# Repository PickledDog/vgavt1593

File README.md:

# vgavt1593
 Marco Maccaferri's Propeller VT100 Terminal, in a box

## Overview
This is a remix of Marco Maccaferri's [VGA Serial Terminal](https://github.com/maccasoft/propeller-vt100-terminal) for RC2014. It is specifically adapted to be used with Stephen C Cousins' [SC131](https://smallcomputercentral.wordpress.com/sc131-z180-pocket-computer/) Z180 pocket computer. It fits into the same Hammond 1593N enclosure, making for a neat and tidy setup when combined with an SC131. Of course, it can also be used with any other retrocomputer or device that expects a VT100-like terminal, connected over "TTL-Serial" raw RS232.

VGA terminal stacked with SC131 computer

## Terminal description
Details about the terminal itself are covered by Marco's project (this remix largely just changes the form factor). For detailed information, see his [project page](https://github.com/maccasoft/propeller-vt100-terminal).

## Serial interfaces
Connection to a computer is provided through an FTDI-style pin header, wired to the same pinout. Specifically, it is wired as a DTE (just like an FTDI dongle), so it can be wired directly to a DCE (like an SC131). A second *passthrough* port is provided to permit a PC connection to the same computer. This passthrough port is wired as a DCE, so FTDI cables can be connected directly. An AND gate mixes the terminal and passthrough connections together, so both can be used simultaneously. Transmitting from both at the same time will send gibberish; in testing this is relatively rare, and XMODEM at least will retransmit if this happens.

## Usage
This terminal lets you use your SC131 (or other retrocomputer) standalone, without dependency on another computer. In addition, a modern computer can be connected to the passthrough port as needed. This is useful for sending files over XMODEM, for example.

### Power
5V power is received through a standard 5.5/2.1mm barrel jack connection, center positive. The device optionally sends power to the connected computer (selectable by a jumper on JP1 - this is expected by SC131). In most cases, JP1 should be left installed. Wall adapters in this voltage and configuration are common, or a USB to 5.5mm cable can be used (examples [here](https://www.ebay.com/sch/i.html?_nkw=usb+to+5.5mm)).

### Why are the plugs on the front?
Because I ran out of room on the enclosure's panels. Between two FTDI headers, 5V in, reset, power switch, VGA, and USB, there wasn't even room left for a power LED. The serial ports are on the same side as the SC131 ones at least, so those can be connected together cleanly with a [6-pin Dupont cable](https://www.ebay.com/sch/i.html?_nkw=6+pin+dupont+cable).

### Initial setup
The parts specified are not pre-programmed; they will need to be programmed before use. Either a [Prop-Plug](https://www.mouser.com/ProductDetail/32201) can be used on the assembled board, or a [TL866](https://www.ebay.com/sch/i.html?_nkw=tl866ii+plus) or [CH341](https://www.ebay.com/sch/i.html?_nkw=ch341a+programmer) can be used on the bare EEPROM. Instructions (and firmware) for programming can be found at the same [link](https://github.com/maccasoft/propeller-vt100-terminal) as above.

## Part selection
Bill Of Materials and part references are below. Note that the right-angle headers have to be a specific type to align with the panel PCBs - they need to have the plastic "end stopper" on the "business" side of the angle, *not* the side you solder to the PCB. Headers from [Pololu](https://www.pololu.com/product/967), [Sparkfun](https://www.sparkfun.com/products/553), and [Adafruit](https://www.adafruit.com/product/1540) are like this, as is the Mouser listing below. Most eBay etc listings are ***not*** like this, and will not align correctly. If the appropriate headers cannot be sourced, double-row right-angle headers can be used, with the top row of pins removed.

The other headers can be snapped from regular breakaway header, for which eBay is substantially cheaper; the Mouser listings are provided for convenience. The specified parts are just the ones I used, and can be substituted as needed - Mouser links provided for convenience and reference. The case is available in other colours!

| Reference | Value | Qty | Mouser link |
| --------- | ----- | --- | ----------- |
| BZ1 | Piezo buzzer | 1 | [TDK PS1240P02BT](https://www.mouser.com/ProductDetail/810-PS1240P02BT) |
| C1, C2 | 1μF ceramic | 2 | [TDK FG18X5R1H105KRT06](https://www.mouser.com/ProductDetail/FG18X5R1H105KRT06) |
| C3-C7 | 100nF ceramic | 5 | [KEMET C315C104M5U5TA](https://www.mouser.com/ProductDetail/C315C104M5U5TA7303) |
| C8 | 10μF electrolytic | 1 | [Nichicon UMA1E100MDD](https://www.mouser.com/ProductDetail/UMA1E100MDD) |
| J1 | 5.5/2.1mm barrel socket | 1 | [CUI PJ-002A](https://www.mouser.com/ProductDetail/490-PJ-002A) |
| J2 | 1x4 header | 1 | [Amphenol 10129378-904002BLF](https://www.mouser.com/ProductDetail/10129378-904002BLF) |
| J3, J4 | 1x6 right-angle header | 2 | [Amphenol 10129379-906003BLF](https://www.mouser.com/ProductDetail/10129379-906003BLF) |
| J5 | USB A socket | 1 | [Amphenol FCI 87520-1110BLF](https://www.mouser.com/ProductDetail/649-87520-1110BLF) |
| J6 | D-Sub HD-15 Female | 1 | [TE 2311763-1](https://www.mouser.com/ProductDetail/571-2311763-1) |
| JP1 | 1x2 header | 1 | [Amphenol 10129378-902002BLF](https://www.mouser.com/ProductDetail/10129378-902002BLF) |
| | jumper | 1 | [Harwin M7583-46](https://www.mouser.com/ProductDetail/M7583-46)
| R1, R4 | 10kΩ resistor | 2 | [Yageo CFR-25JT-52-10K](https://www.mouser.com/ProductDetail/CFR-25JT-52-10K) |
| R2, R3 | 4k7Ω resistor | 2 | [Yageo CFR-25JT-52-4K7](https://www.mouser.com/ProductDetail/CFR-25JT-52-4K7) |
| R5, R8 | 47kΩ resistor | 2 | [Yageo CFR-25JT-52-47K](https://www.mouser.com/ProductDetail/CFR-25JT-52-47K) |
| R6, R7 | 47Ω resistor | 2 | [Yageo CFR-25JT-52-47R](https://www.mouser.com/ProductDetail/CFR-25JT-52-47R) |
| R9, R12, R15 | 261Ω resistor | 3 | [Yageo MFR-25FRF52-261R](https://www.mouser.com/ProductDetail/603-MFR-25FRF52-261R) |
| R10, R13, R16 | 510Ω resistor | 3 | [Yageo MFR-25FTE52-510R](https://www.mouser.com/ProductDetail/603-MFR-25FTE52-510R) |
| R11, R14, R17-R19 | 120Ω resistor | 5 | [Yageo MFR-25FTF52-120R](https://www.mouser.com/ProductDetail/603-MFR-25FTF52-120R) |
| SW1 | SPDT toggle sw, right-angle | 1 | [Grayhill 34CMSP12B2M7QT](https://www.mouser.com/ProductDetail/706-34CMSP12B2M7QT) |
| SW2 | Right-angle tact sw 8.3mm | 1 | [C&K PTS645VL832LFS](https://www.mouser.com/ProductDetail/611-PTS645VL832) |
| U1 | Parallax Propeller | 1 | [Parallax Propeller P8X32A-D40](https://www.mouser.com/ProductDetail/619-P8X32A-D40) |
| | socket | 1 | [Amphenol DILB40P-223TLF](https://www.mouser.com/ProductDetail/DILB40P-223TLF) |
| U2 | 24LC256 EEPROM | 1 | [Microchip 24LC256](https://www.mouser.com/ProductDetail/579-24LC256-I-P) |
| | socket | 1 | [Amphenol DILB8P-223TLF](https://www.mouser.com/ProductDetail/DILB8P-223TLF) |
| U3 | MCP1700-330 | 1 | [Microchip MCP1700-3302E/TO](https://www.mouser.com/ProductDetail/579-MCP1700-3302E-TO) |
| U4 | 74HC08 | 1 | [TI SN74HC08AN](https://www.mouser.com/ProductDetail/595-SN74HC08AN) |
| X1 | 5MHz HC-49 crystal | 1 | [ECS ECS-50-18-4XEN](https://www.mouser.com/ProductDetail/520-50-18-4XEN) |
| Case | Hammond 1593N | 1 | [Hammond 1593NTBU](https://www.mouser.com/ProductDetail/546-1593NTBU) |
| Screws | Hammond self-tapping | (some of) | [Hammond 1593ATS](https://www.mouser.com/ProductDetail/546-1593ATS100) |

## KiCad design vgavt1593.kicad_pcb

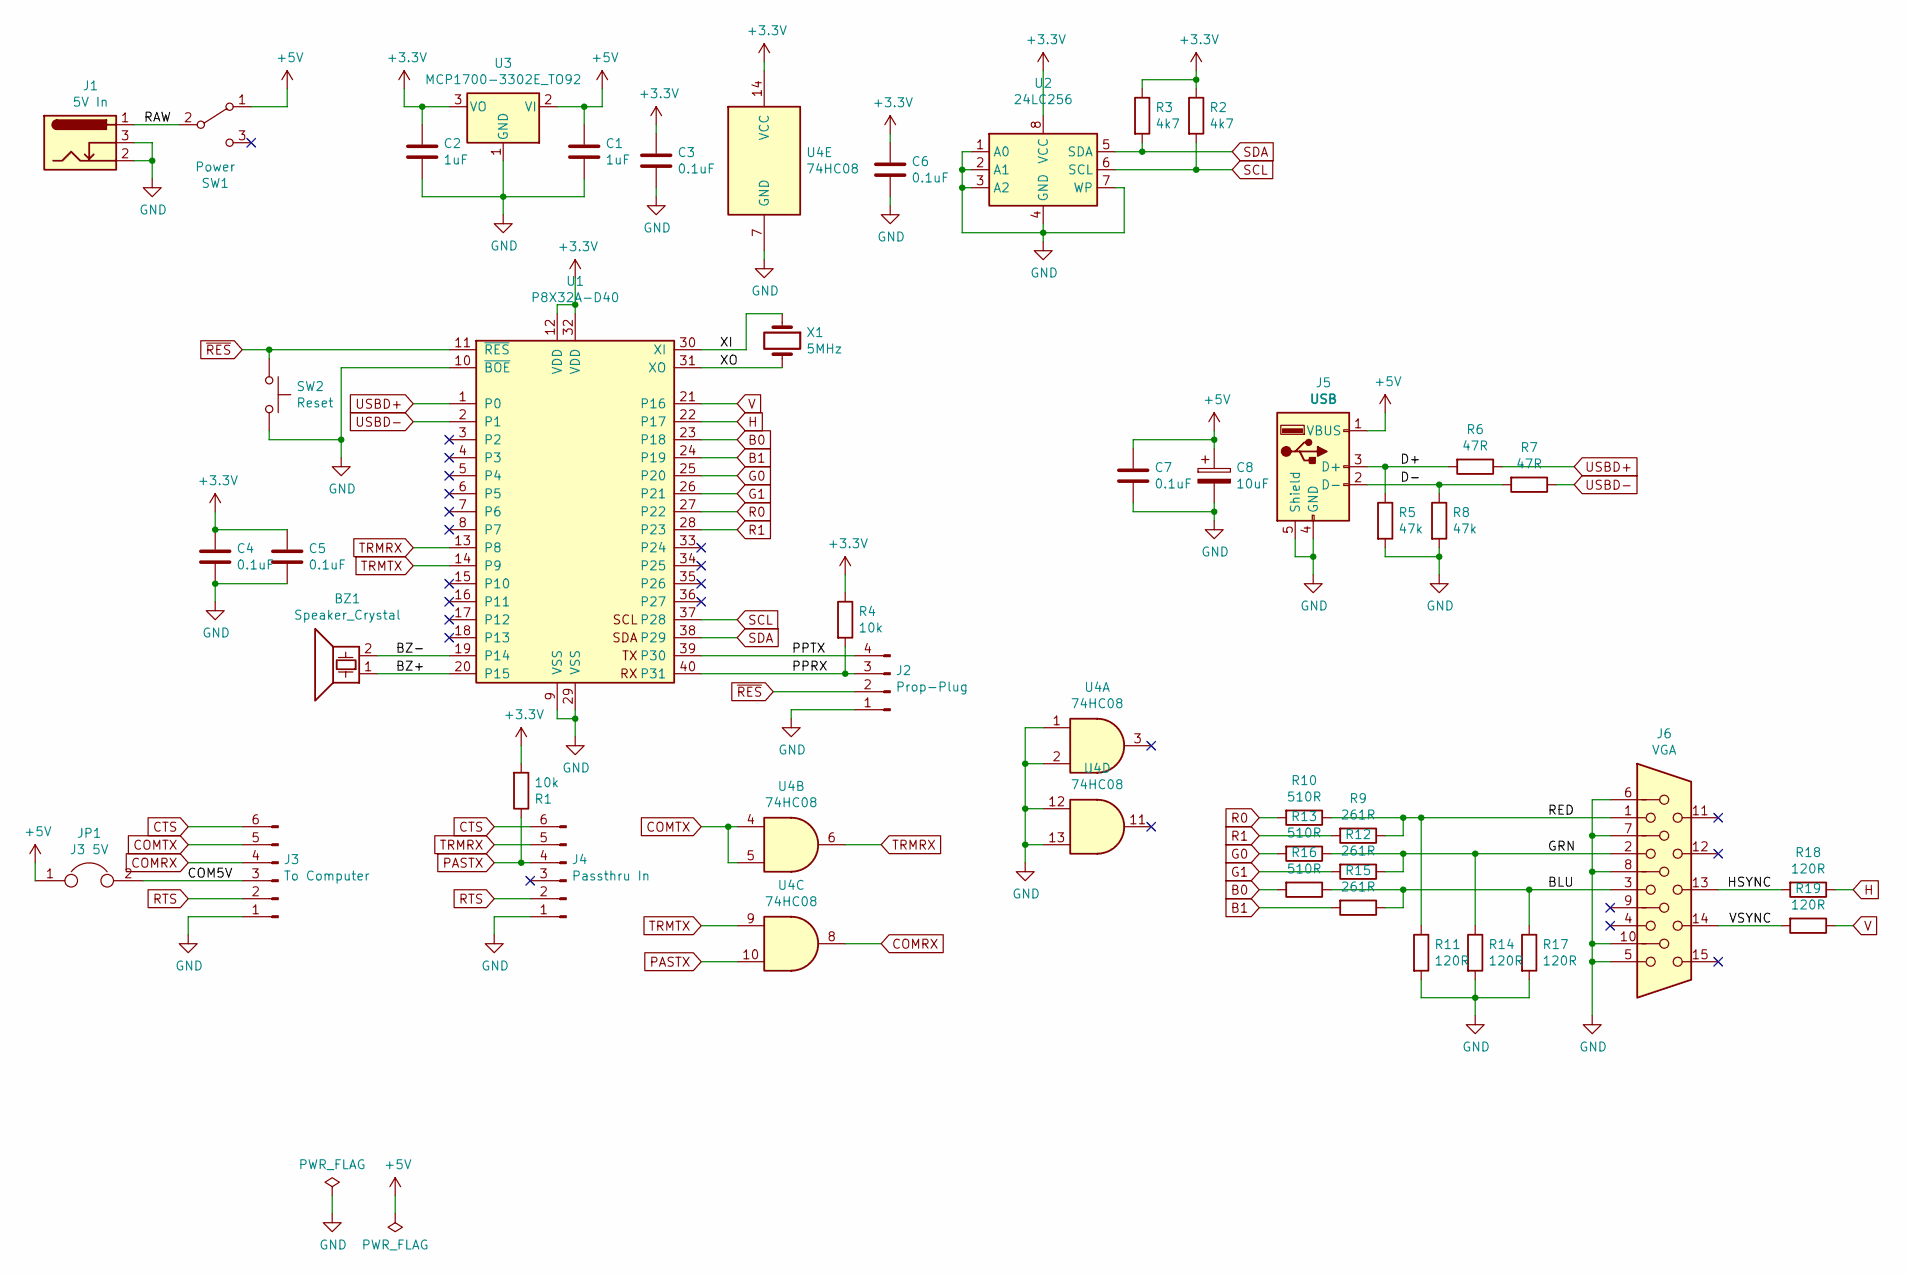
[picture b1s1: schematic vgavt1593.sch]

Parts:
BZ1: Speaker_Crystal; Buzzer_TDK_PS1240P02BT_D12.2mm_H6.5mm
C1, C2: 1uF; C_Disc_D3.0mm_W1.6mm_P2.50mm
C3, C4, C5, C6, C7: 0.1uF; C_Disc_D3.0mm_W1.6mm_P2.50mm
C8: 10uF; CP_Radial_D5.0mm_P2.00mm
J1: 5V In; BarrelJack_Horizontal
J2: Prop-Plug; PinHeader_1x04_P2.54mm_Vertical
J3: To Computer; PinHeader_1x06_P2.54mm_Vertical
J4: Passthru In; PinHeader_1x06_P2.54mm_Vertical
J5: USB; USB_A_CONNFLY_DS1095-WNR0
J6: VGA; DSUB-15-HD_Female_Horizontal_P2.29x2.54mm_Housed
JP1: J3 5V; PinHeader_1x02_P2.54mm_Vertical
R1, R4: 10k; R_Axial_DIN0207_L6.3mm_D2.5mm_P7.62mm_Horizontal
R2, R3: 4k7; R_Axial_DIN0207_L6.3mm_D2.5mm_P7.62mm_Horizontal
R5, R8: 47k; R_Axial_DIN0207_L6.3mm_D2.5mm_P7.62mm_Horizontal
R6, R7: 47R; R_Axial_DIN0207_L6.3mm_D2.5mm_P7.62mm_Horizontal
R9, R12, R15: 261R; R_Axial_DIN0207_L6.3mm_D2.5mm_P7.62mm_Horizontal
R10, R13, R16: 510R; R_Axial_DIN0207_L6.3mm_D2.5mm_P7.62mm_Horizontal
R11, R14, R17, R18, R19: 120R; R_Axial_DIN0207_L6.3mm_D2.5mm_P7.62mm_Horizontal
SW1: Power; SW_Toggle_SPDT_Vertical
SW2: Reset; SW_Tactile_SPST_Angled_PTS645Vx83-2LFS
U1: P8X32A-D40; DIP-40_W15.24mm_LongPads
U2: 24LC256; DIP-8_W7.62mm_LongPads
U3: MCP1700-3302E_TO92; TO-92
U4: 74HC08; DIP-14_W7.62mm_LongPads
X1: 5MHz; Crystal_HC49-U_Vertical

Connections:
+3V3: C2.1, C3.1, C4.1, C5.1, C6.1, R1.2, R2.1, R3.1, R4.1, U1.12 (VDD), U1.32 (VDD), U2.8 (VCC), U3.3 (VO), U4.14 (VCC)
+5V: C1.1, C7.1, C8.1, J5.1 (VBUS), JP1.1, SW1.1 (A), U3.2 (VI)
/BLU: J6.3, R15.1, R16.1, R17.1
/BZ+: BZ1.1, U1.20 (P15)
/BZ-: BZ1.2, U1.19 (P14)
/COM5V: J3.3, JP1.2
/D+: J5.3 (D+), R5.1, R6.2
/D-: J5.2 (D-), R7.2, R8.1
/GRN: J6.2, R12.1, R13.1, R14.1
/HSYNC: J6.13, R18.2
/PPRX: J2.3, R4.2, U1.40 (P31)
/PPTX: J2.4, U1.39 (P30)
/RAW: J1.1, SW1.2 (B)
/RED: J6.1, R9.1, R10.1, R11.1
/VSYNC: J6.14, R19.2
/XI: U1.30 (XI), X1.1
/XO: U1.31 (XO), X1.2
B0: R16.2, U1.23 (P18)
B1: R15.2, U1.24 (P19)
COMRX: J3.4, U4.8
COMTX: J3.5, U4.4, U4.5
CTS: J3.6, J4.6
G0: R13.2, U1.25 (P20)
G1: R12.2, U1.26 (P21)
GND: C1.2, C2.2, C3.2, C4.2, C5.2, C6.2, C7.2, C8.2, J1.2, J1.3, J2.1, J3.1, J4.1, J5.4 (GND), J5.5 (Shield), J6.5, J6.6, J6.7, J6.8, J6.10, R5.2, R8.2, R11.2, R14.2, R17.2, SW2.1, U1.9 (VSS), U1.10 (~BOE), U1.29 (VSS), U2.1 (A0), U2.2 (A1), U2.3 (A2), U2.4 (GND), U2.7 (WP), U3.1 (GND), U4.1, U4.2, U4.7 (GND), U4.12, U4.13
H: R18.1, U1.22 (P17)
PASTX: J4.4, R1.1, U4.10
R0: R10.2, U1.27 (P22)
R1: R9.2, U1.28 (P23)
RTS: J3.2, J4.2
SCL: R2.2, U1.37 (P28), U2.6 (SCL)
SDA: R3.2, U1.38 (P29), U2.5 (SDA)
TRMRX: J4.5, U1.13 (P8), U4.6
TRMTX: U1.14 (P9), U4.9
USBD+: R6.1, U1.1 (P0)
USBD-: R7.1, U1.2 (P1)
V: R19.1, U1.21 (P16)
~RES: J2.2, SW2.2, U1.11 (~RES)

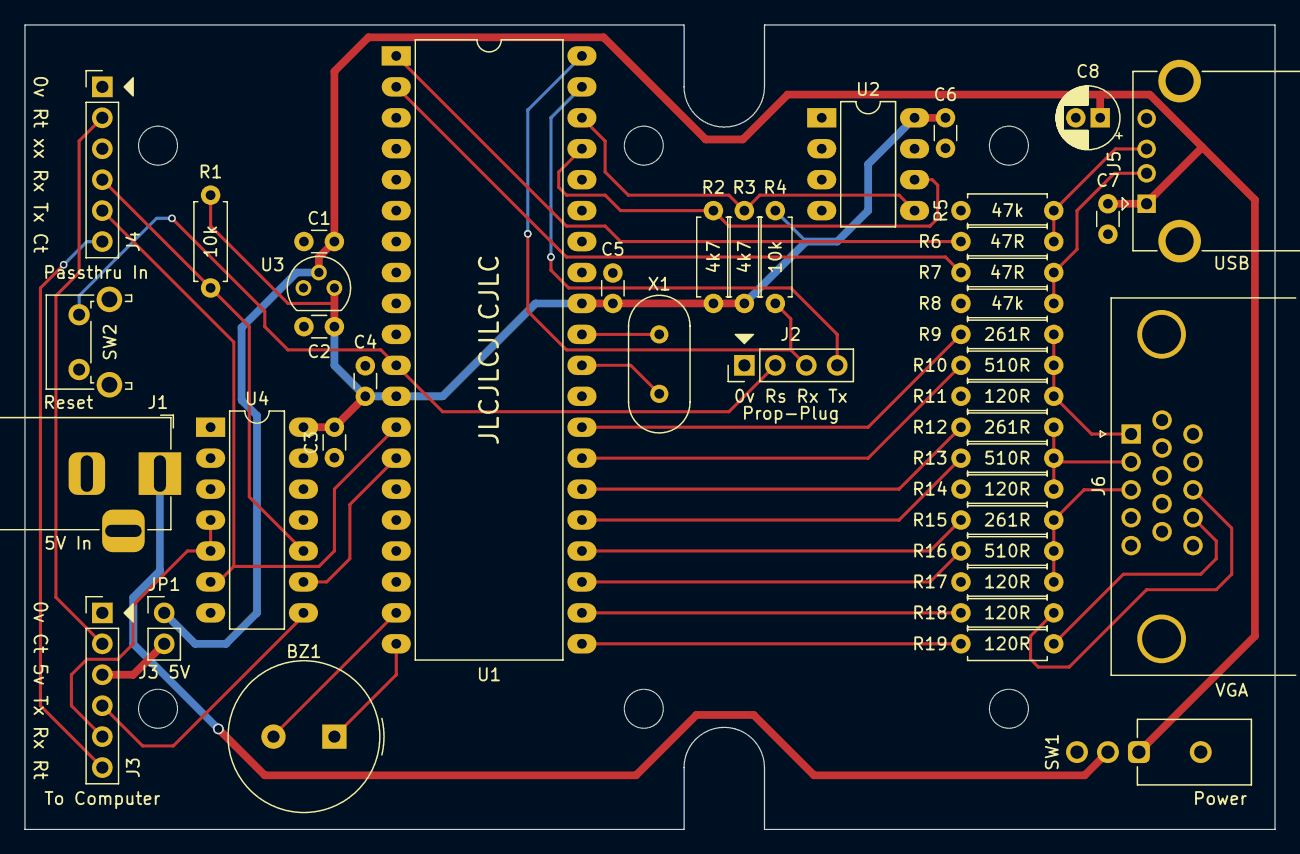
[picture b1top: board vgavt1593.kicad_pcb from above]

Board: 2 copper layers, 102.6 x 66.0 mm, 48 parts (0 on the bottom side), 38 nets.

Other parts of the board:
MK1, MK2, MK3, MK4, MK5, MK6: Mounting_Hole; MountingHole_3.2mm_M3_ISO7380

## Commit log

2020-11-23 Initial commit of vgavt1593
    Initial commit of vgavt1593/PD102
2020-12-09 Add README and images
    Add README and images of completed widget
2020-12-09 Fix README table
2020-12-09 Update README.md
    Add case links and programming notes
2020-12-09 Update README.md
    Fix bad Markdown
2020-12-09 UART dyslexia
2020-12-11 Tweak README and BOM
2020-12-12 Tweak component references
2020-12-13 Fix README typos
2020-12-27 Update README.md
    Added link to buy Dupont cable

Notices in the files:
vgavt1593.kicad_pcb:
(C) 2017 Marco Maccaferri
(C) 2020 Wesley Isacks
